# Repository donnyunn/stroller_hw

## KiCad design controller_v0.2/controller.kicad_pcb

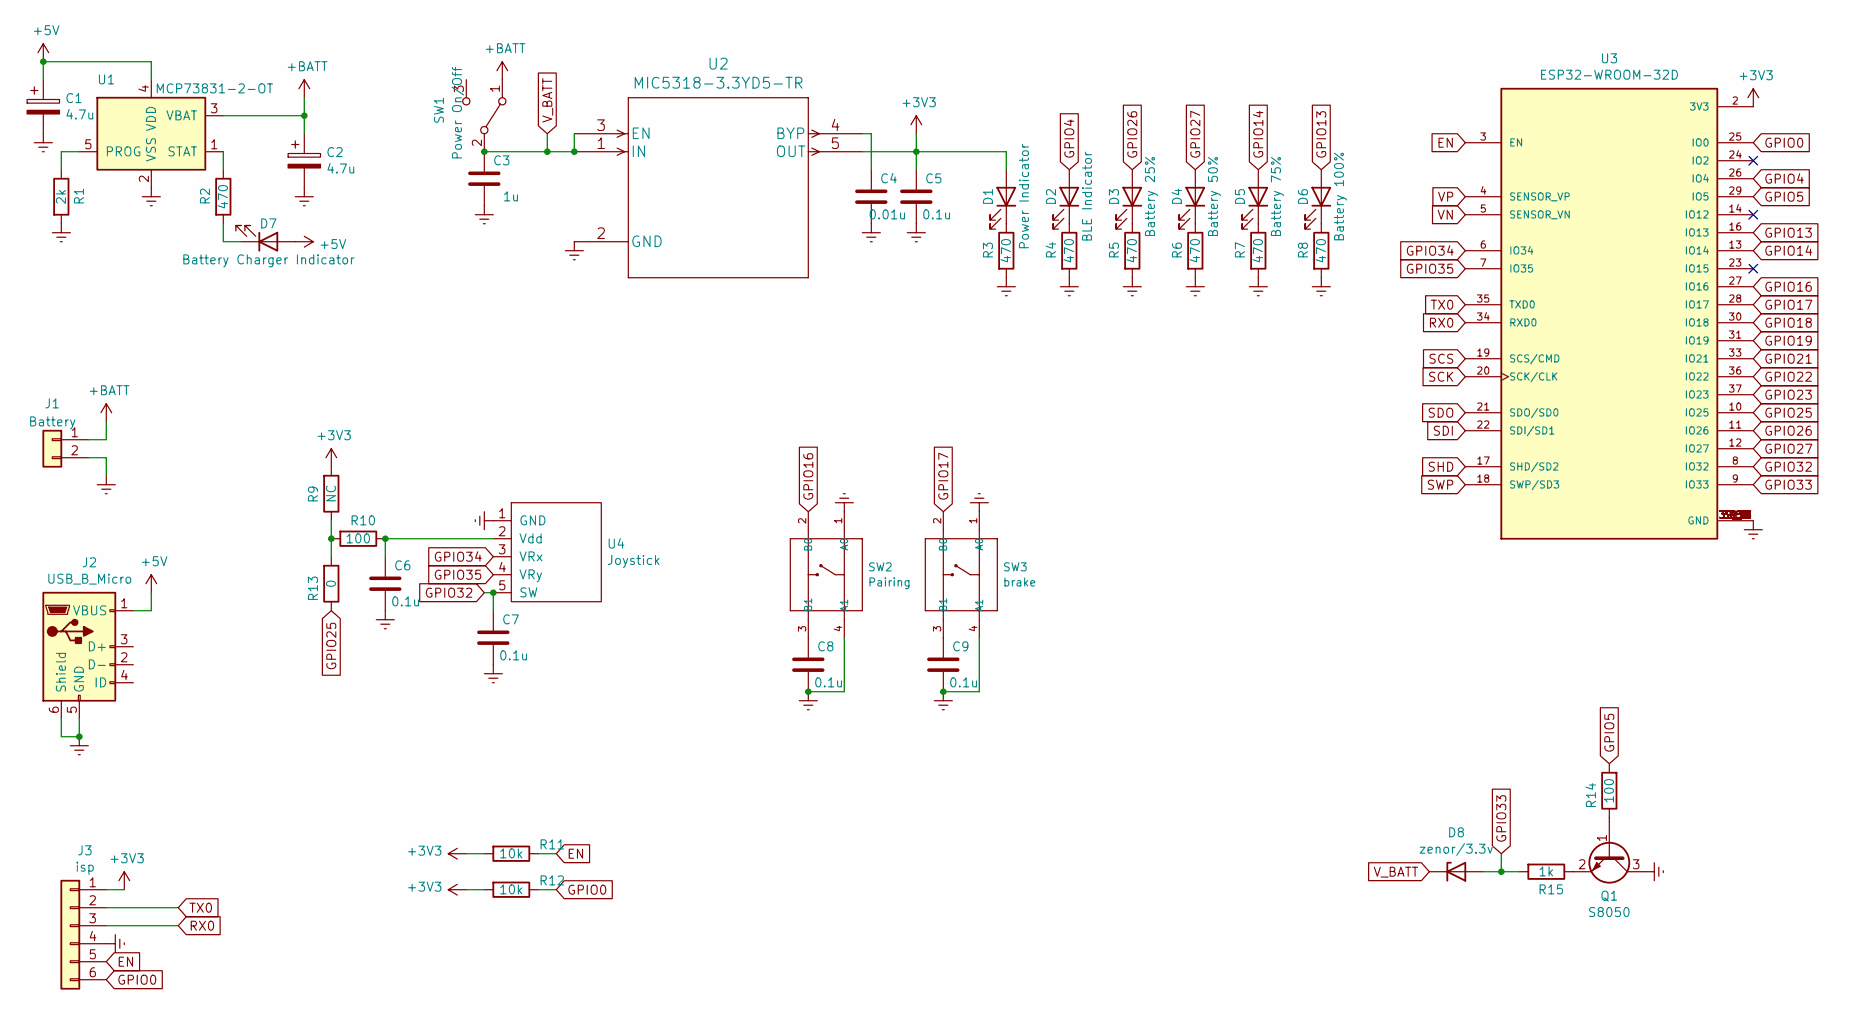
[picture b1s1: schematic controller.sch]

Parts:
C1, C2: 4.7u; CP_EIA-3216-18_Kemet-A; MPN TAJA475K006RNJ
C3: 1u; C_0603_1608Metric_Pad1.08x0.95mm_HandSolder; MPN CL10A105KQ8NNNC
C4: 0.01u; C_0603_1608Metric_Pad1.08x0.95mm_HandSolder; MPN CL10B103KB8NNNC
C5, C6, C7, C8, C9: 0.1u; C_0603_1608Metric_Pad1.08x0.95mm_HandSolder; MPN CL10B104KB8NNNL
D1: Power Indicator; LED_0805_2012Metric_Pad1.15x1.40mm_HandSolder; MPN WR148UW-W
D2: BLE Indicator; LED_0805_2012Metric_Pad1.15x1.40mm_HandSolder; MPN WR148UW-W
D3: Battery 25%; LED_0805_2012Metric_Pad1.15x1.40mm_HandSolder; MPN WR148UW-W
D4: Battery 50%; LED_0805_2012Metric_Pad1.15x1.40mm_HandSolder; MPN WR148UW-W
D5: Battery 75%; LED_0805_2012Metric_Pad1.15x1.40mm_HandSolder; MPN WR148UW-W
D6: Battery 100%; LED_0805_2012Metric_Pad1.15x1.40mm_HandSolder; MPN WR148UW-W
D7: Battery Charger Indicator; LED_0805_2012Metric_Pad1.15x1.40mm_HandSolder; MPN WR148UW-W
D8: zenor/3.3v; D_T-1_P5.08mm_Horizontal
J1: Battery; Molex_PicoBlade_53261-0271_1x02-1MP_P1.25mm_Horizontal; MPN 0532610271
J2: USB_B_Micro; USB_Micro-B_GCT_USB3076-30-A; MPN USB3076-30-A
J3: isp; JST_PH_B6B-PH-K_1x06_P2.00mm_Vertical; MPN B6B-PH-K-S(LF)(SN)
Q1: S8050; SOT-23
R1: 2k; R_0603_1608Metric_Pad0.98x0.95mm_HandSolder; MPN RC0603FR-072KL
R2, R3, R4, R5, R6, R7, R8: 470; R_0603_1608Metric_Pad0.98x0.95mm_HandSolder; MPN RC0603JR-07470RL
R9: NC; R_0603_1608Metric_Pad0.98x0.95mm_HandSolder
R10: 100; R_0603_1608Metric_Pad0.98x0.95mm_HandSolder; MPN RC0603JR-07100RL
R11, R12: 10k; R_0603_1608Metric_Pad0.98x0.95mm_HandSolder; MPN AC0603JR-0710KL
R13: 0; R_0603_1608Metric_Pad0.98x0.95mm_HandSolder; MPN RC0603FR-070RL
R14: 100; R_0603_1608Metric_Pad0.98x0.95mm_HandSolder
R15: 1k; R_0603_1608Metric_Pad0.98x0.95mm_HandSolder
SW1: Power On/Off; PinHeader_1x03_P2.54mm_Vertical
SW2: Pairing; SW4-6.0X6.0X5.0MM; MPN TS-1105-8MM
SW3: brake; SW4-6.0X6.0X5.0MM; MPN TS-1105
U1: MCP73831-2-OT; SOT-23-5; MPN MCP73831T-2ACI/OT
U2: MIC5318-3.3YD5-TR; MPN MIC5318-3.3YD5-TR
U3: ESP32-WROOM-32D; MODULE_ESP32-WROOM-32D; MPN ESP32-WROOM-32D
U4: Joystick; EPX389MK; MPN 조이스틱 스위치-TS

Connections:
+3V3: C5.1, D1.2 (A), J3.1, R9.2, R11.2, R12.2, U2.5 (OUT), U3.2 (3V3)
+5V: C1.1, D7.2 (A), J2.1 (VBUS), U1.4 (VDD)
+BATT: C2.1, J1.1, SW1.1 (A), U1.3 (VBAT)
EN: J3.5, R11.1, U3.3 (EN)
Earth: C1.2, C2.2, C3.2, C4.2, C5.2, C6.2, C7.2, C8.2, C9.2, J1.2, J2.5 (GND), J2.6 (Shield), J3.4, Q1.3 (C), R1.2, R3.2, R4.2, R5.2, R6.2, R7.2, R8.2, SW2.1 (A0), SW2.4 (A1), SW3.1 (A0), SW3.4 (A1), U1.2 (VSS), U2.2 (GND), U3.1 (GND), U3.15 (GND), U3.38 (GND), U3.39_1 (GND), U3.39_2 (GND), U3.39_3 (GND), U3.39_4 (GND), U3.39_5 (GND), U3.39_6 (GND), U3.39_7 (GND), U3.39_8 (GND), U3.39_9 (GND), U3.39_10 (GND), U3.39_11 (GND), U3.39_12 (GND), U3.39_13 (GND), U3.39_14 (GND), U3.39_15 (GND), U3.39_16 (GND), U3.39_17 (GND), U3.39_18 (GND), U3.39_19 (GND), U3.39_20 (GND), U3.39_21 (GND), U4.1 (GND)
GPIO0: J3.6, R12.1, U3.25 (IO0)
GPIO4: D2.2 (A), U3.26 (IO4)
GPIO5: R14.2, U3.29 (IO5)
GPIO13: D6.2 (A), U3.16 (IO13)
GPIO14: D5.2 (A), U3.13 (IO14)
GPIO16: SW2.2 (B0), U3.27 (IO16)
GPIO17: SW3.2 (B0), U3.28 (IO17)
GPIO18: U3.30 (IO18)
GPIO19: U3.31 (IO19)
GPIO21: U3.33 (IO21)
GPIO22: U3.36 (IO22)
GPIO23: U3.37 (IO23)
GPIO25: R13.1, U3.10 (IO25)
GPIO26: D3.2 (A), U3.11 (IO26)
GPIO27: D4.2 (A), U3.12 (IO27)
GPIO32: C7.1, U3.8 (IO32), U4.5 (SW)
GPIO33: D8.2 (A), R15.2, U3.9 (IO33)
GPIO34: U3.6 (IO34), U4.3 (VRx)
GPIO35: U3.7 (IO35), U4.4 (VRy)
unnamed: C4.1, U2.4 (BYP)
unnamed: C6.1, R10.1, U4.2 (Vdd)
unnamed: C8.1, SW2.3 (B1)
unnamed: C9.1, SW3.3 (B1)
unnamed: D1.1 (K), R3.1
unnamed: D2.1 (K), R4.1
unnamed: D3.1 (K), R5.1
unnamed: D4.1 (K), R6.1
unnamed: D5.1 (K), R7.1
unnamed: D6.1 (K), R8.1
unnamed: D7.1 (K), R2.2
unnamed: Q1.1 (B), R14.1
unnamed: Q1.2 (E), R15.1
unnamed: R1.1, U1.5 (PROG)
unnamed: R2.1, U1.1 (STAT)
unnamed: R9.1, R10.2, R13.2
RX0: J3.3, U3.34 (RXD0)
SCK: U3.20 (SCK/CLK)
SCS: U3.19 (SCS/CMD)
SDI: U3.22 (SDI/SD1)
SDO: U3.21 (SDO/SD0)
SHD: U3.17 (SHD/SD2)
SWP: U3.18 (SWP/SD3)
TX0: J3.2, U3.35 (TXD0)
VN: U3.5 (SENSOR_VN)
VP: U3.4 (SENSOR_VP)
V_BATT: C3.1, D8.1 (K), SW1.2 (B), U2.1 (IN), U2.3 (EN)

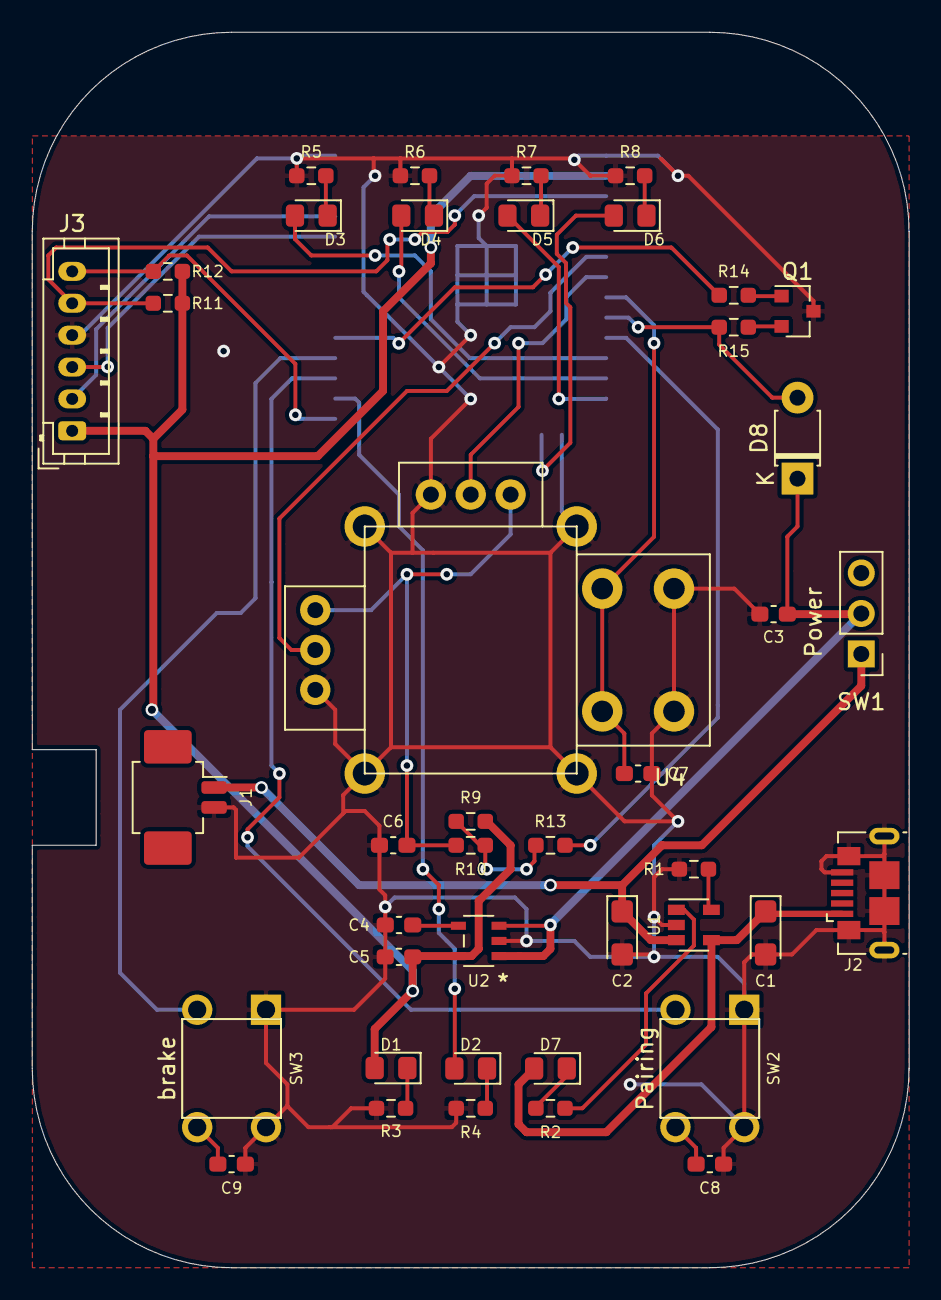
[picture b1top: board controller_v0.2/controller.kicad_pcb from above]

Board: 2 copper layers, 55.0 x 77.5 mm, 43 parts (1 on the bottom side), 38 nets.

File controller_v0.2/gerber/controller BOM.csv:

Reference, Quantity, Value, Footprint, Datasheet, MPN
C1 C2 ,2,"4.7u","Capacitor_Tantalum_SMD:CP_EIA-3216-18_Kemet-A","https://www.digikey.kr/product-detail/ko/avx-corporation/TAJ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","TAJA475K006RNJ"
C3 ,1,"1u","Capacitor_SMD:C_0603_1608Metric_Pad1.08x0.95mm_HandSolder","https://www.digikey.kr/product-detail/ko/samsung-electro-mec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","CL10A105KQ8NNNC"
C4 ,1,"0.01u","Capacitor_SMD:C_0603_1608Metric_Pad1.08x0.95mm_HandSolder","https://www.digikey.kr/product-detail/ko/samsung-electro-mec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","CL10B103KB8NNNC"
C5 C6 C7 C8 C9 C10 ,6,"0.1u","Capacitor_SMD:C_0603_1608Metric_Pad1.08x0.95mm_HandSolder","https://www.digikey.kr/product-detail/ko/samsung-electro-mec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","CL10B104KB8NNNL"
D1 ,1,"Power Indicator","LED_SMD:LED_0805_2012Metric_Pad1.15x1.40mm_HandSolder","https://www.eleparts.co.kr/goods/view?no=8104621","WR148UW-W"
D2 ,1,"BLE Indicator","LED_SMD:LED_0805_2012Metric_Pad1.15x1.40mm_HandSolder","https://www.eleparts.co.kr/goods/view?no=8104621","WR148UW-W"
D3 ,1,"Battery 25%","LED_SMD:LED_0805_2012Metric_Pad1.15x1.40mm_HandSolder","https://www.eleparts.co.kr/goods/view?no=8104621","WR148UW-W"
D4 ,1,"Battery 50%","LED_SMD:LED_0805_2012Metric_Pad1.15x1.40mm_HandSolder","https://www.eleparts.co.kr/goods/view?no=8104621","WR148UW-W"
D5 ,1,"Battery 75%","LED_SMD:LED_0805_2012Metric_Pad1.15x1.40mm_HandSolder","https://www.eleparts.co.kr/goods/view?no=8104621","WR148UW-W"
D6 ,1,"Battery 100%","LED_SMD:LED_0805_2012Metric_Pad1.15x1.40mm_HandSolder","https://www.eleparts.co.kr/goods/view?no=8104621","WR148UW-W"
D7 ,1,"Battery Charger Indicator","LED_SMD:LED_0805_2012Metric_Pad1.15x1.40mm_HandSolder","https://www.eleparts.co.kr/goods/view?no=8104621","WR148UW-W"
J1 ,1,"Battery","Connector_Molex:Molex_PicoBlade_53261-0271_1x02-1MP_P1.25mm_Horizontal","https://www.digikey.kr/product-detail/ko/molex/0532610271/WM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","0532610271"
J2 ,1,"USB_B_Micro","Connector_USB:USB_Micro-B_GCT_USB3076-30-A","https://www.digikey.kr/product-detail/ko/gct/USB3076-30-A/20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","USB3076-30-A"
J3 ,1,"isp","Connector_JST:JST_PH_B6B-PH-K_1x06_P2.00mm_Vertical","https://www.eleparts.co.kr/goods/view?no=7600842","B6B-PH-K-S(LF)(SN)"
R1 ,1,"2k","Resistor_SMD:R_0603_1608Metric_Pad0.98x0.95mm_HandSolder","https://www.digikey.kr/product-detail/ko/yageo/RC0603FR-072K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","RC0603FR-072KL"
R10 ,1,"100","Resistor_SMD:R_0603_1608Metric_Pad0.98x0.95mm_HandSolder","https://www.digikey.kr/product-detail/ko/yageo/RC0603JR-0710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","RC0603JR-07100RL"
R11 R12 R14 R15 ,4,"10k","Resistor_SMD:R_0603_1608Metric_Pad0.98x0.95mm_HandSolder","https://www.digikey.kr/product-detail/ko/yageo/AC0603JR-0710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","AC0603JR-0710KL"
R13 ,1,"0","Resistor_SMD:R_0603_1608Metric_Pad0.98x0.95mm_HandSolder","https://www.digikey.kr/product-detail/ko/yageo/RC0603FR-070R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","RC0603FR-070RL"
R16 R17 ,2,"1k","Resistor_SMD:R_0603_1608Metric_Pad0.98x0.95mm_HandSolder","https://www.digikey.kr/product-detail/ko/yageo/RC0603JR-071K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","RC0603JR-071KL"
R2 R3 R4 R5 R6 R7 R8 ,7,"470","Resistor_SMD:R_0603_1608Metric_Pad0.98x0.95mm_HandSolder","https://www.digikey.kr/product-detail/ko/yageo/RC0603JR-0747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","RC0603JR-07470RL"
R9 ,1,"NC","Resistor_SMD:R_0603_1608Metric_Pad0.98x0.95mm_HandSolder","~"
SW1 ,1,"Power On/Off","Connector_PinHeader_2.54mm:PinHeader_1x03_P2.54mm_Vertical","~"
SW2 ,1,"Pairing","OPL_Switch:SW4-6.0X6.0X5.0MM","https://www.eleparts.co.kr/goods/view?no=2630843","TS-1105-8MM"
SW3 ,1,"brake","OPL_Switch:SW4-6.0X6.0X5.0MM","","TS-1105"
U1 ,1,"MCP73831-2-OT","Package_TO_SOT_SMD:SOT-23-5","http://ww1.microchip.com/downloads/en/DeviceDoc/20001984g.pdf","MCP73831T-2ACI/OT"
U2 ,1,"MIC5318-3.3YD5-TR","MIC531833YD5TR:MIC5318-3.3YD5-TR","https://www.digikey.kr/product-detail/ko/microchip-technolog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","MIC5318-3.3YD5-TR"
U3 ,1,"ESP32-WROOM-32D","ESP32-WROOM-32D:MODULE_ESP32-WROOM-32D","https://www.digikey.kr/product-detail/ko/espressif-systems/E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","ESP32-WROOM-32D"
U4 ,1,"Joystick","EPK389MK:EPX389MK","https://www.eleparts.co.kr/goods/view?no=32769","조이스틱 스위치-TS"
U5 ,1,"MAX17048G+T10","MAX17048G_T10:MAX17048G_T10","https://www.digikey.kr/product-detail/ko/maxim-integrated/MA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","MAX17048G+T10"

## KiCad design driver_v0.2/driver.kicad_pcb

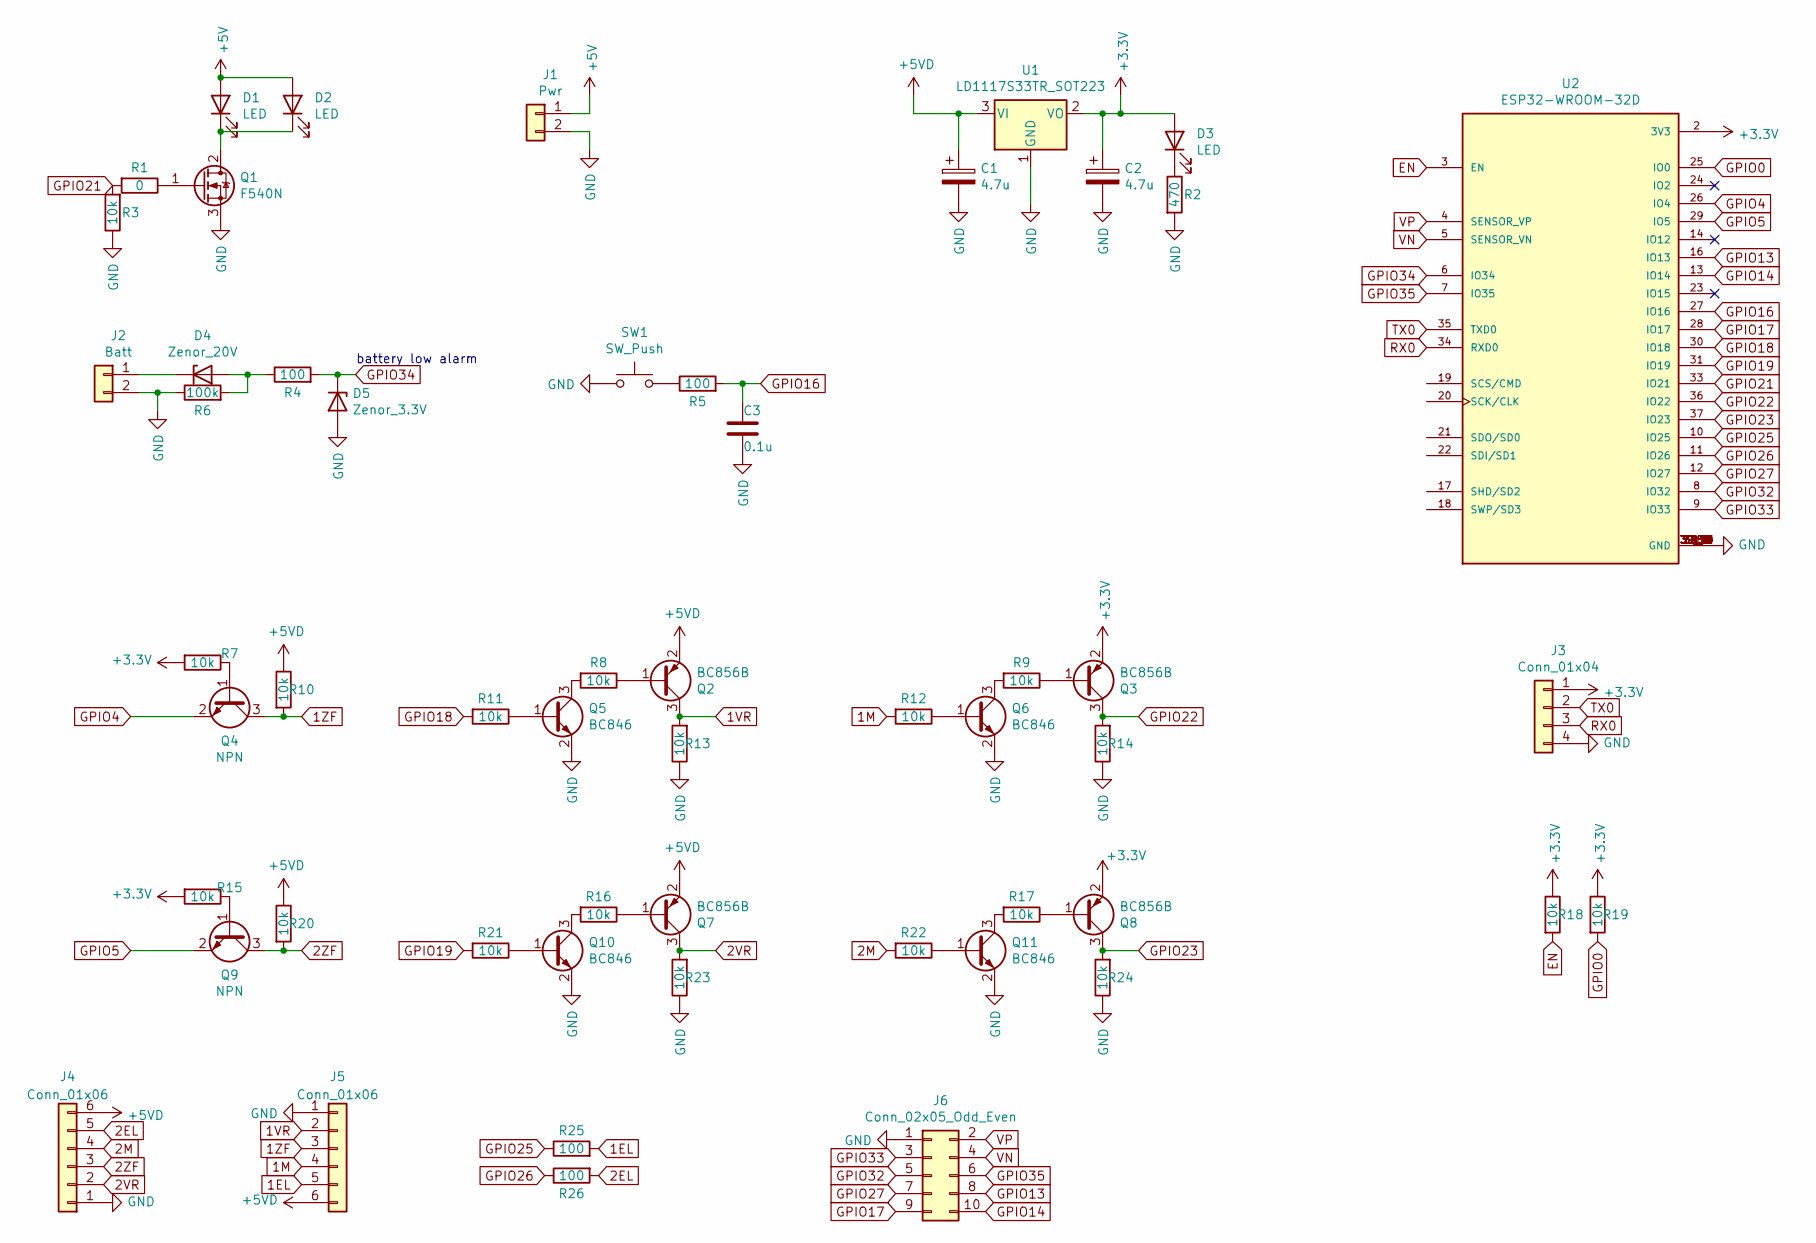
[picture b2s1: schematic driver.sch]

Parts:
C1, C2: 4.7u; CP_EIA-3216-18_Kemet-A
C3: 0.1u; C_0603_1608Metric_Pad1.08x0.95mm_HandSolder
D1, D2: LED; LED_D5.0mm
D3: LED; LED_0805_2012Metric_Pad1.15x1.40mm_HandSolder; MPN WR148UW-W
D4: Zenor_20V; D_DO-41_SOD81_P7.62mm_Horizontal; MPN 1N4747A
D5: Zenor_3.3V; D_DO-41_SOD81_P7.62mm_Horizontal; MPN 1N5226B
J1: Pwr; PinHeader_1x02_P2.54mm_Vertical
J2: Batt; PinHeader_1x02_P2.54mm_Vertical
J3: Conn_01x04; PinHeader_1x04_P2.54mm_Vertical
J4, J5: Conn_01x06; JST_PH_B6B-PH-K_1x06_P2.00mm_Vertical
J6: Conn_02x05_Odd_Even; PinHeader_2x05_P2.54mm_Vertical
Q1: F540N; TO-220-3_Vertical
Q2, Q3, Q7, Q8: BC856B; SOT-23
Q4, Q9: NPN; SOT-23; MPN S8050
Q5, Q6, Q10, Q11: BC846; SOT-23
R1: 0; R_0603_1608Metric_Pad0.98x0.95mm_HandSolder
R2: 470; R_0603_1608Metric_Pad0.98x0.95mm_HandSolder
R3, R7, R8, R9, R10, R11, R12, R13, R14, R15, R16, R17, R18, R19, R20, R21, R22, R23, R24: 10k; R_0603_1608Metric_Pad0.98x0.95mm_HandSolder
R4, R5, R25, R26: 100; R_0603_1608Metric_Pad0.98x0.95mm_HandSolder
R6: 100k; R_0603_1608Metric_Pad0.98x0.95mm_HandSolder
SW1: SW_Push; SW_PUSH_6mm; MPN TS-1105-8MM
U1: LD1117S33TR_SOT223; SOT-223-3_TabPin2; MPN ZLDO1117QG33TA
U2: ESP32-WROOM-32D; ESP32-WROOM-32; PARTREV 1.9

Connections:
1EL: J5.5, R25.2
1M: J5.4, R12.2
1VR: J5.2, Q2.3 (C), R13.2
1ZF: J5.3, Q4.3 (C), R10.2
2EL: J4.5, R26.2
2M: J4.4, R22.2
2VR: J4.2, Q7.3 (C), R23.2
2ZF: J4.3, Q9.3 (C), R20.2
+3V3: C2.1, D3.2 (A), J3.1, Q3.2 (E), Q8.2 (E), R7.2, R15.2, R18.1, R19.1, U1.2 (VO), U2.2 (3V3)
+5V: D1.2 (A), D2.2 (A), J1.1
+5VD: C1.1, J4.6, J5.6, Q2.2 (E), Q7.2 (E), R10.1, R20.1, U1.3 (VI)
EN: R18.2, U2.3 (EN)
GND: C1.2, C2.2, C3.2, D5.2 (A), J1.2, J2.2, J3.4, J4.1, J5.1, J6.1, Q1.3 (S), Q5.2 (E), Q6.2 (E), Q10.2 (E), Q11.2 (E), R2.2, R3.1, R6.1, R13.1, R14.1, R23.1, R24.1, SW1.1, U1.1 (GND), U2.1 (GND), U2.15 (GND), U2.38 (GND), U2.39_1 (GND), U2.39_2 (GND), U2.39_3 (GND), U2.39_4 (GND), U2.39_5 (GND), U2.39_6 (GND), U2.39_7 (GND), U2.39_8 (GND), U2.39_9 (GND), U2.39_10 (GND), U2.39_11 (GND), U2.39_12 (GND), U2.39_13 (GND), U2.39_14 (GND), U2.39_15 (GND), U2.39_16 (GND), U2.39_17 (GND), U2.39_18 (GND), U2.39_19 (GND), U2.39_20 (GND), U2.39_21 (GND)
GPIO0: R19.2, U2.25 (IO0)
GPIO4: Q4.2 (E), U2.26 (IO4)
GPIO5: Q9.2 (E), U2.29 (IO5)
GPIO13: J6.8, U2.16 (IO13)
GPIO14: J6.10, U2.13 (IO14)
GPIO16: C3.1, R5.2, U2.27 (IO16)
GPIO17: J6.9, U2.28 (IO17)
GPIO18: R11.2, U2.30 (IO18)
GPIO19: R21.2, U2.31 (IO19)
GPIO21: R1.2, R3.2, U2.33 (IO21)
GPIO22: Q3.3 (C), R14.2, U2.36 (IO22)
GPIO23: Q8.3 (C), R24.2, U2.37 (IO23)
GPIO25: R25.1, U2.10 (IO25)
GPIO26: R26.1, U2.11 (IO26)
GPIO27: J6.7, U2.12 (IO27)
GPIO32: J6.5, U2.8 (IO32)
GPIO33: J6.3, U2.9 (IO33)
GPIO34: D5.1 (K), R4.2, U2.6 (IO34)
GPIO35: J6.6, U2.7 (IO35)
unnamed: D1.1 (K), D2.1 (K), Q1.2 (D)
unnamed: D3.1 (K), R2.1
unnamed: D4.1 (K), J2.1
unnamed: D4.2 (A), R4.1, R6.2
unnamed: Q1.1 (G), R1.1
unnamed: Q2.1 (B), R8.1
unnamed: Q3.1 (B), R9.1
unnamed: Q4.1 (B), R7.1
unnamed: Q5.1 (B), R11.1
unnamed: Q5.3 (C), R8.2
unnamed: Q6.1 (B), R12.1
unnamed: Q6.3 (C), R9.2
unnamed: Q7.1 (B), R16.1
unnamed: Q8.1 (B), R17.1
unnamed: Q9.1 (B), R15.1
unnamed: Q10.1 (B), R21.1
unnamed: Q10.3 (C), R16.2
unnamed: Q11.1 (B), R22.1
unnamed: Q11.3 (C), R17.2
unnamed: R5.1, SW1.2
RX0: J3.3, U2.34 (RXD0)
TX0: J3.2, U2.35 (TXD0)
VN: J6.4, U2.5 (SENSOR_VN)
VP: J6.2, U2.4 (SENSOR_VP)

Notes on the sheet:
battery low alarm

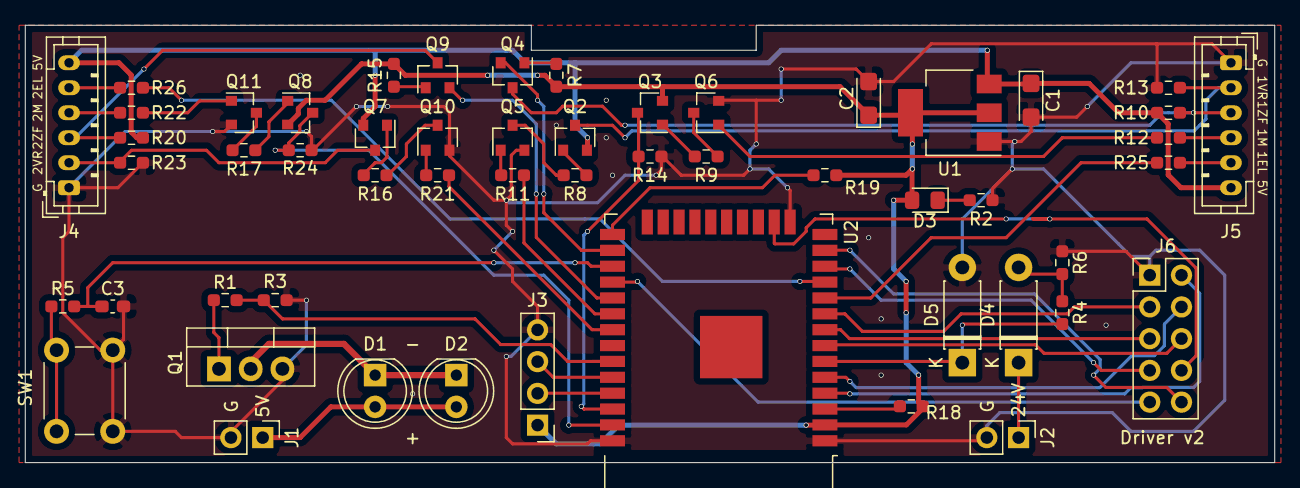
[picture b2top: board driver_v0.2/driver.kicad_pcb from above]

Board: 2 copper layers, 100.0 x 35.0 mm, 54 parts (0 on the bottom side), 56 nets.

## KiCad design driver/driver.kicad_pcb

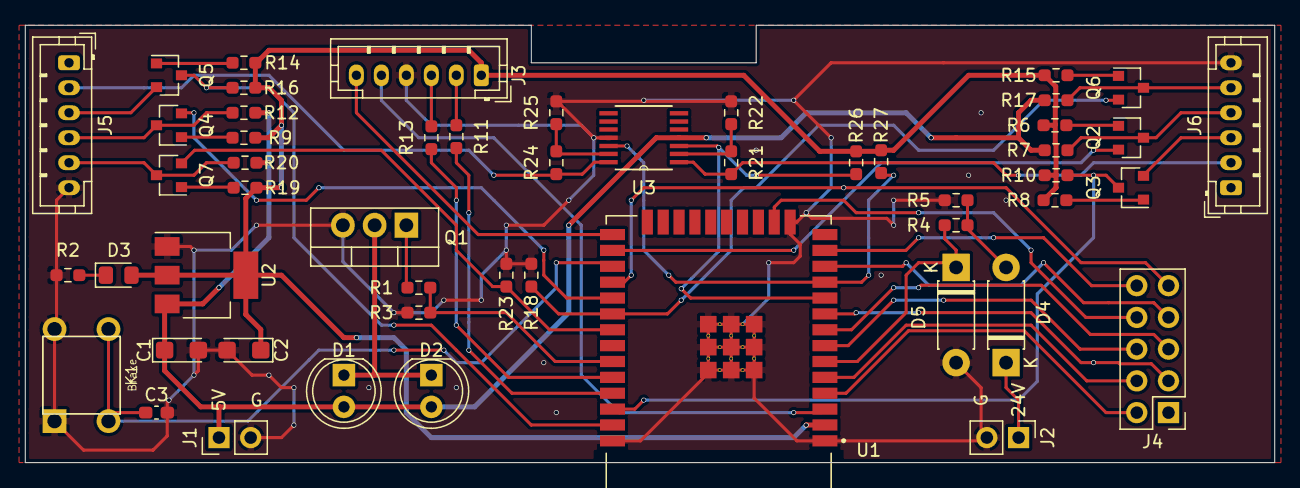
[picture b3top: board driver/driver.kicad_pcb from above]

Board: 2 copper layers, 100.0 x 35.0 mm, 52 parts (0 on the bottom side), 50 nets.

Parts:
C1, C2: 4.7u; CP_EIA-3216-18_Kemet-A
C3: 0.1u; C_0603_1608Metric_Pad1.08x0.95mm_HandSolder
D1, D2: LED; LED_D5.0mm
D3: LED; LED_0805_2012Metric_Pad1.15x1.40mm_HandSolder
D4: Zenor_20V; D_DO-41_SOD81_P7.62mm_Horizontal
D5: Zenor_3.3V; D_DO-41_SOD81_P7.62mm_Horizontal
J1: Pwr; PinHeader_1x02_P2.54mm_Vertical
J2: Batt; PinHeader_1x02_P2.54mm_Vertical
J3: isp; JST_PH_B6B-PH-K_1x06_P2.00mm_Vertical
J4: Conn_02x05_Odd_Even; PinHeader_2x05_P2.54mm_Vertical
J5, J6: Conn_01x06; JST_PH_B6B-PH-K_1x06_P2.00mm_Vertical
K1: Brake; SW4-6.0X6.0X5.0MM
Q1: IRF540N; TO-220-3_Vertical
Q2, Q3, Q4, Q5, Q6, Q7: NPN; SOT-23
R1, R11, R13, R18, R22, R23, R25: 1k; R_0603_1608Metric_Pad0.98x0.95mm_HandSolder
R2: 470; R_0603_1608Metric_Pad0.98x0.95mm_HandSolder
R3, R6, R7, R8, R9, R10, R12, R14, R15, R16, R17, R19, R20, R26, R27: 10k; R_0603_1608Metric_Pad0.98x0.95mm_HandSolder
R4: 100; R_0603_1608Metric_Pad0.98x0.95mm_HandSolder
R5: 100k; R_0603_1608Metric_Pad0.98x0.95mm_HandSolder
R21, R24: 560; R_0603_1608Metric_Pad0.98x0.95mm_HandSolder
U1: ESP32-WROOM-32D; MODULE_ESP32-WROOM-32D
U2: LD1117S33TR_SOT223; SOT-223-3_TabPin2
U3: MCP6044T-I_ST; MCP6044T

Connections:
1EL: J6.2, R21.2, U3.1
1M: J6.3, Q3.2
1VR: J6.5, Q6.3, R17.2
1ZF: J6.4, Q2.3, R7.2
2EL: J5.2, R24.2, U3.14
2M: J5.3, Q5.2
2VR: J5.5, Q7.3, R20.2
2ZF: J5.4, Q4.3, R12.2
+3V3: C2.1, D3.2, J3.1, R6.2, R8.2, R9.2, R10.1, R14.2, R15.2, R16.1, R19.2, R26.2, R27.2, U1.2, U2.2
+5V: C1.1, D1.2, D2.2, J1.1, R7.1, R12.1, R17.1, R20.1, U2.3, U3.4
EN: J3.5, U1.3
GND: C1.2, C2.2, C3.2, D5.2, J1.2, J2.2, J3.4, J5.6, J6.6, K1.1, K1.4, Q1.3, R2.2, R3.1, R5.1, R18.2, R22.2, R23.2, R25.2, U1.1, U1.15, U1.38, U1.39_1, U1.39_2, U1.39_3, U1.39_4, U1.39_5, U1.39_6, U1.39_7, U1.39_8, U1.39_9, U1.39_10, U1.39_11, U1.39_12, U1.39_13, U1.39_14, U1.39_15, U1.39_16, U1.39_17, U1.39_18, U1.39_19, U1.39_20, U1.39_21, U2.1, U3.11
GPIO0: J3.6, U1.25
GPIO4: Q2.2, U1.26
GPIO5: Q4.2, U1.29
GPIO13: J4.8, U1.16
GPIO14: J4.10, U1.13
GPIO16: C3.1, K1.2, K1.3, U1.27
GPIO17: J4.9, U1.28
GPIO18: Q6.2, R18.1, U1.30
GPIO19: Q7.2, R23.1, U1.31
GPIO21: R1.2, R3.2, U1.33
GPIO22: Q3.3, R10.2, U1.36
GPIO23: Q5.3, R16.2, U1.37
GPIO25: R26.1, U1.10, U3.3
GPIO26: R27.1, U1.11, U3.12
GPIO27: J4.7, U1.12
GPIO32: J4.5, U1.8
GPIO33: J4.3, U1.9
GPIO34: D5.1, R4.2, U1.6
GPIO35: J4.6, U1.7
unnamed: D1.1, D2.1, Q1.2
unnamed: D3.1, R2.1
unnamed: D4.1, J2.1
unnamed: D4.2, R4.1, R5.2
unnamed: J3.2, R11.2
unnamed: J3.3, R13.2
unnamed: Q1.1, R1.1
unnamed: Q2.1, R6.1
unnamed: Q3.1, R8.1
unnamed: Q4.1, R9.1
unnamed: Q5.1, R14.1
unnamed: Q6.1, R15.1
unnamed: Q7.1, R19.1
unnamed: R21.1, R22.1, U3.2
unnamed: R24.1, R25.1, U3.13
RX0: R13.1, U1.34
TX0: R11.1, U1.35
VN: J4.4, U1.5
VP: J4.2, U1.4

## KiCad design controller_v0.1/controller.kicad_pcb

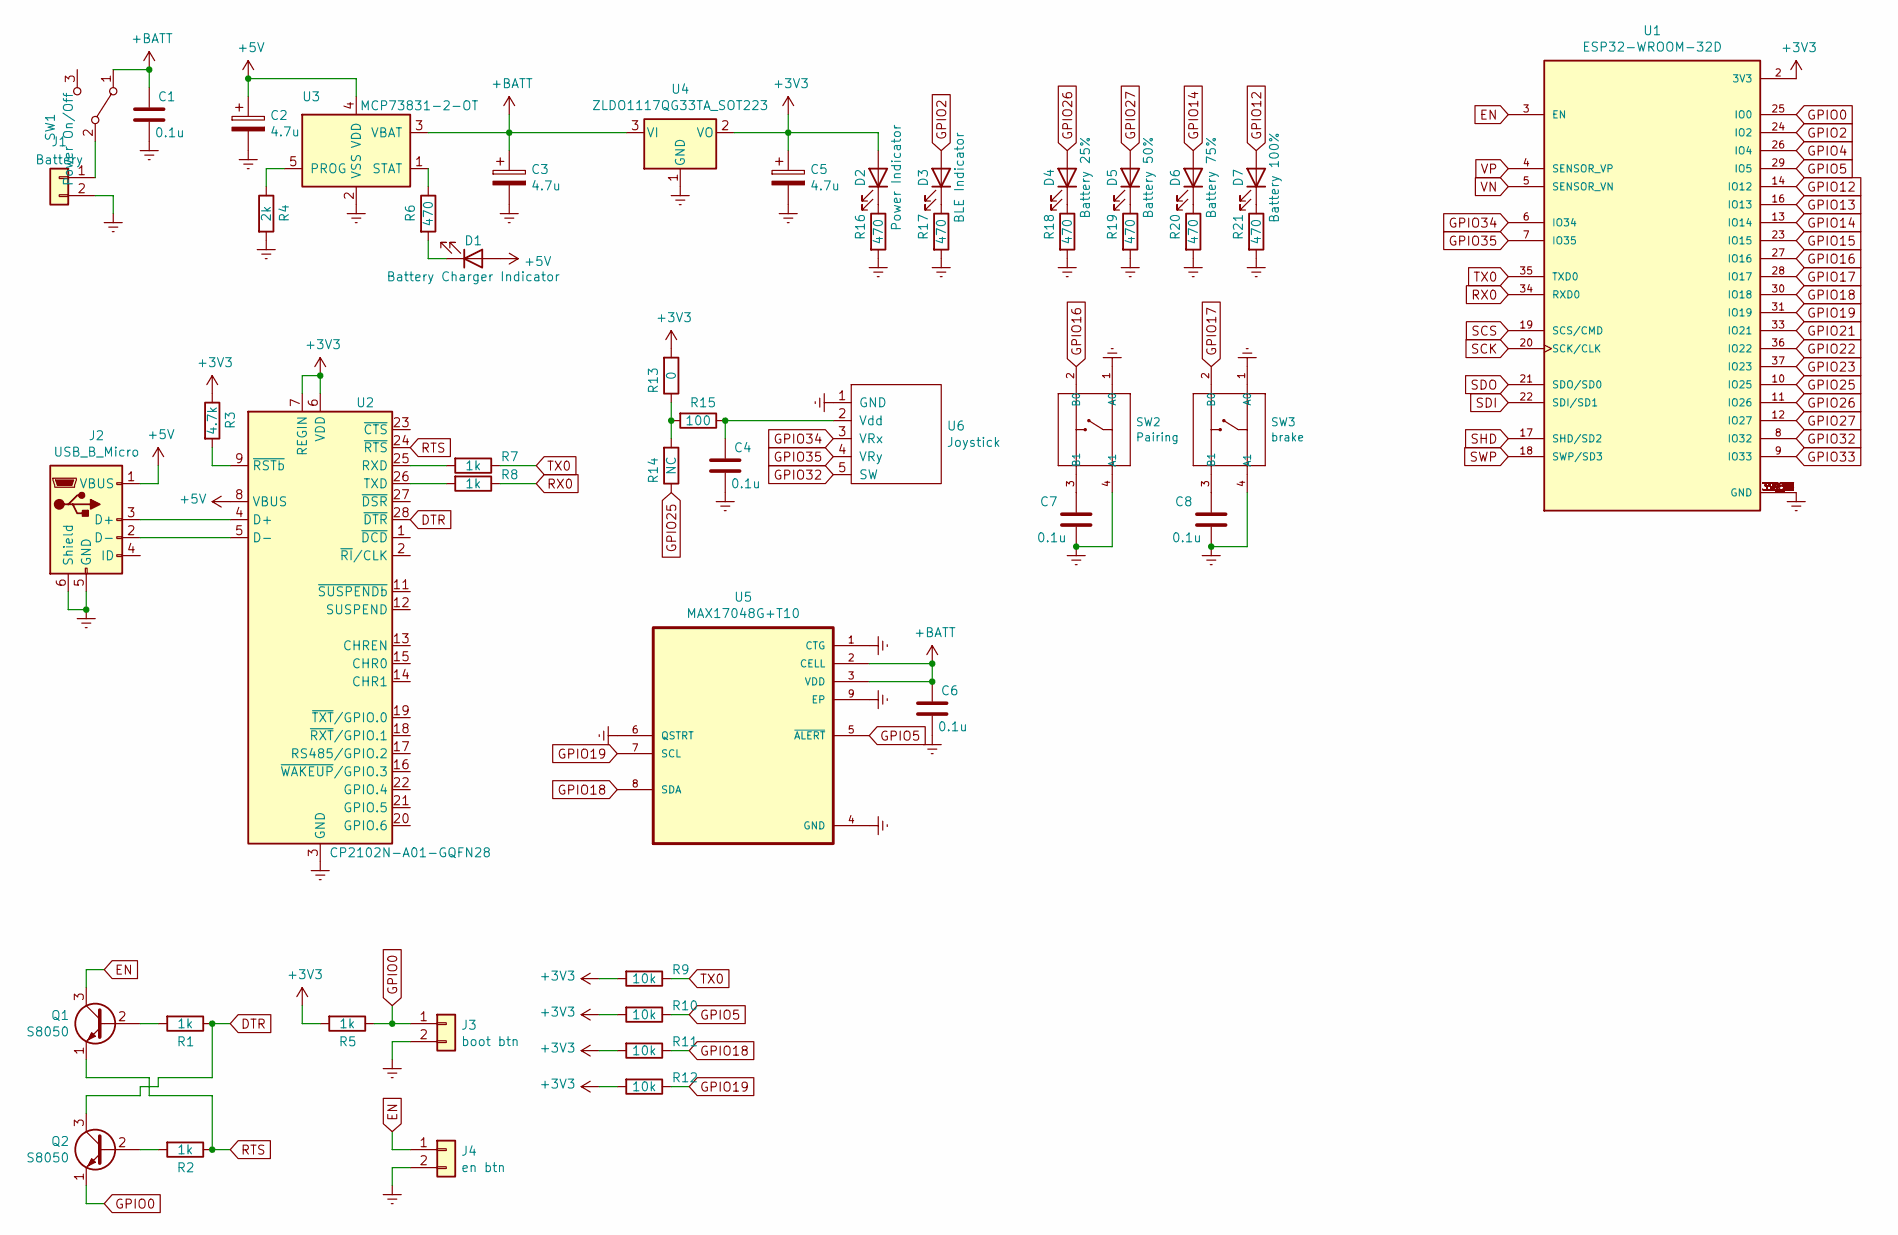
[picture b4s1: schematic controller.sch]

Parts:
C1, C4, C6, C7, C8: 0.1u; C_0603_1608Metric_Pad1.08x0.95mm_HandSolder
C2, C3, C5: 4.7u; CP_EIA-3216-18_Kemet-A
D1: Battery Charger Indicator; LED_D5.0mm
D2: Power Indicator; LED_D5.0mm
D3: BLE Indicator; LED_D5.0mm
D4: Battery 25%; LED_D5.0mm
D5: Battery 50%; LED_D5.0mm
D6: Battery 75%; LED_D5.0mm
D7: Battery 100%; LED_D5.0mm
J1: Battery; Molex_PicoBlade_53261-0271_1x02-1MP_P1.25mm_Horizontal
J2: USB_B_Micro; USB_Micro-B_Molex-105017-0001; MPN 47589-0001
J3: boot btn; PinHeader_1x02_P2.54mm_Vertical
J4: en btn; PinHeader_1x02_P2.54mm_Vertical
Q1, Q2: S8050; SOT-23; MPN S8050
R1, R2, R5, R7, R8: 1k; R_0603_1608Metric_Pad0.98x0.95mm_HandSolder
R3: 4.7k; R_0603_1608Metric_Pad0.98x0.95mm_HandSolder
R4: 2k; R_0603_1608Metric_Pad0.98x0.95mm_HandSolder
R6, R16, R17, R18, R19, R20, R21: 470; R_0603_1608Metric_Pad0.98x0.95mm_HandSolder
R9, R10, R11, R12: 10k; R_0603_1608Metric_Pad0.98x0.95mm_HandSolder
R13: 0; R_0603_1608Metric_Pad0.98x0.95mm_HandSolder
R14: NC; R_0603_1608Metric_Pad0.98x0.95mm_HandSolder
R15: 100; R_0603_1608Metric_Pad0.98x0.95mm_HandSolder
SW1: Power On/Off; PinHeader_1x03_P2.54mm_Vertical
SW2: Pairing; SW4-6.0X6.0X5.0MM; MPN TS-1105
SW3: brake; SW4-6.0X6.0X5.0MM; MPN TS-1105
U1: ESP32-WROOM-32D; MODULE_ESP32-WROOM-32D; PARTREV 1.9
U2: CP2102N-A01-GQFN28; QFN-28-1EP_5x5mm_P0.5mm_EP3.35x3.35mm
U3: MCP73831-2-OT; SOT-23-5; MPN MCP73831T-2ACI/OT
U4: ZLDO1117QG33TA_SOT223; SOT-223-3_TabPin2; MPN ZLDO1117QG33TA
U5: MAX17048G+T10; MAX17048G_T10; MPN MAX17048G+T10
U6: Joystick; EPX389MK

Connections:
+3V3: C5.1, D2.2 (A), R3.1, R5.2, R9.2, R10.2, R11.2, R12.2, R13.2, U1.2 (3V3), U2.6 (VDD), U2.7 (REGIN), U4.2 (VO)
+5V: C2.1, D1.2 (A), J2.1 (VBUS), U2.8 (VBUS), U3.4 (VDD)
+BATT: C1.1, C3.1, C6.1, SW1.1 (A), U3.3 (VBAT), U4.3 (VI), U5.2 (CELL), U5.3 (VDD)
DTR: Q2.3 (C), R1.1, U2.28 (~DTR)
EN: J4.1, Q1.3 (C), U1.3 (EN)
Earth: C1.2, C2.2, C3.2, C4.2, C5.2, C6.2, C7.2, C8.2, J1.2, J2.5 (GND), J2.6 (Shield), J3.2, J4.2, R4.2, R16.2, R17.2, R18.2, R19.2, R20.2, R21.2, SW2.1 (A0), SW2.4 (A1), SW3.1 (A0), SW3.4 (A1), U1.1 (GND), U1.15 (GND), U1.38 (GND), U1.39_1 (GND), U1.39_2 (GND), U1.39_3 (GND), U1.39_4 (GND), U1.39_5 (GND), U1.39_6 (GND), U1.39_7 (GND), U1.39_8 (GND), U1.39_9 (GND), U1.39_10 (GND), U1.39_11 (GND), U1.39_12 (GND), U1.39_13 (GND), U1.39_14 (GND), U1.39_15 (GND), U1.39_16 (GND), U1.39_17 (GND), U1.39_18 (GND), U1.39_19 (GND), U1.39_20 (GND), U1.39_21 (GND), U2.3 (GND), U2.29 (GND), U3.2 (VSS), U4.1 (GND), U5.1 (CTG), U5.4 (GND), U5.6 (QSTRT), U5.9 (EP), U6.1 (GND)
GPIO0: J3.1, Q2.1 (E), R5.1, U1.25 (IO0)
GPIO2: D3.2 (A), U1.24 (IO2)
GPIO4: U1.26 (IO4)
GPIO5: R10.1, U1.29 (IO5), U5.5 (~ALERT)
GPIO12: D7.2 (A), U1.14 (IO12)
GPIO13: U1.16 (IO13)
GPIO14: D6.2 (A), U1.13 (IO14)
GPIO15: U1.23 (IO15)
GPIO16: SW2.2 (B0), U1.27 (IO16)
GPIO17: SW3.2 (B0), U1.28 (IO17)
GPIO18: R11.1, U1.30 (IO18), U5.8 (SDA)
GPIO19: R12.1, U1.31 (IO19), U5.7 (SCL)
GPIO21: U1.33 (IO21)
GPIO22: U1.36 (IO22)
GPIO23: U1.37 (IO23)
GPIO25: R14.1, U1.10 (IO25)
GPIO26: D4.2 (A), U1.11 (IO26)
GPIO27: D5.2 (A), U1.12 (IO27)
GPIO32: U1.8 (IO32), U6.5 (SW)
GPIO33: U1.9 (IO33)
GPIO34: U1.6 (IO34), U6.3 (VRx)
GPIO35: U1.7 (IO35), U6.4 (VRy)
unnamed: C4.1, R15.1, U6.2 (Vdd)
unnamed: C7.1, SW2.3 (B1)
unnamed: C8.1, SW3.3 (B1)
unnamed: D1.1 (K), R6.2
unnamed: D2.1 (K), R16.1
unnamed: D3.1 (K), R17.1
unnamed: D4.1 (K), R18.1
unnamed: D5.1 (K), R19.1
unnamed: D6.1 (K), R20.1
unnamed: D7.1 (K), R21.1
unnamed: J1.1, SW1.2 (B)
unnamed: J2.2 (D-), U2.5 (D-)
unnamed: J2.3 (D+), U2.4 (D+)
unnamed: Q1.2 (B), R1.2
unnamed: Q2.2 (B), R2.2
unnamed: R3.2, U2.9 (~RSTb)
unnamed: R4.1, U3.5 (PROG)
unnamed: R6.1, U3.1 (STAT)
unnamed: R7.2, U2.25 (RXD)
unnamed: R8.2, U2.26 (TXD)
unnamed: R13.1, R14.2, R15.2
RTS: Q1.1 (E), R2.1, U2.24 (~RTS)
RX0: R8.1, U1.34 (RXD0)
SCK: U1.20 (SCK/CLK)
SCS: U1.19 (SCS/CMD)
SDI: U1.22 (SDI/SD1)
SDO: U1.21 (SDO/SD0)
SHD: U1.17 (SHD/SD2)
SWP: U1.18 (SWP/SD3)
TX0: R7.1, R9.1, U1.35 (TXD0)
VN: U1.5 (SENSOR_VN)
VP: U1.4 (SENSOR_VP)

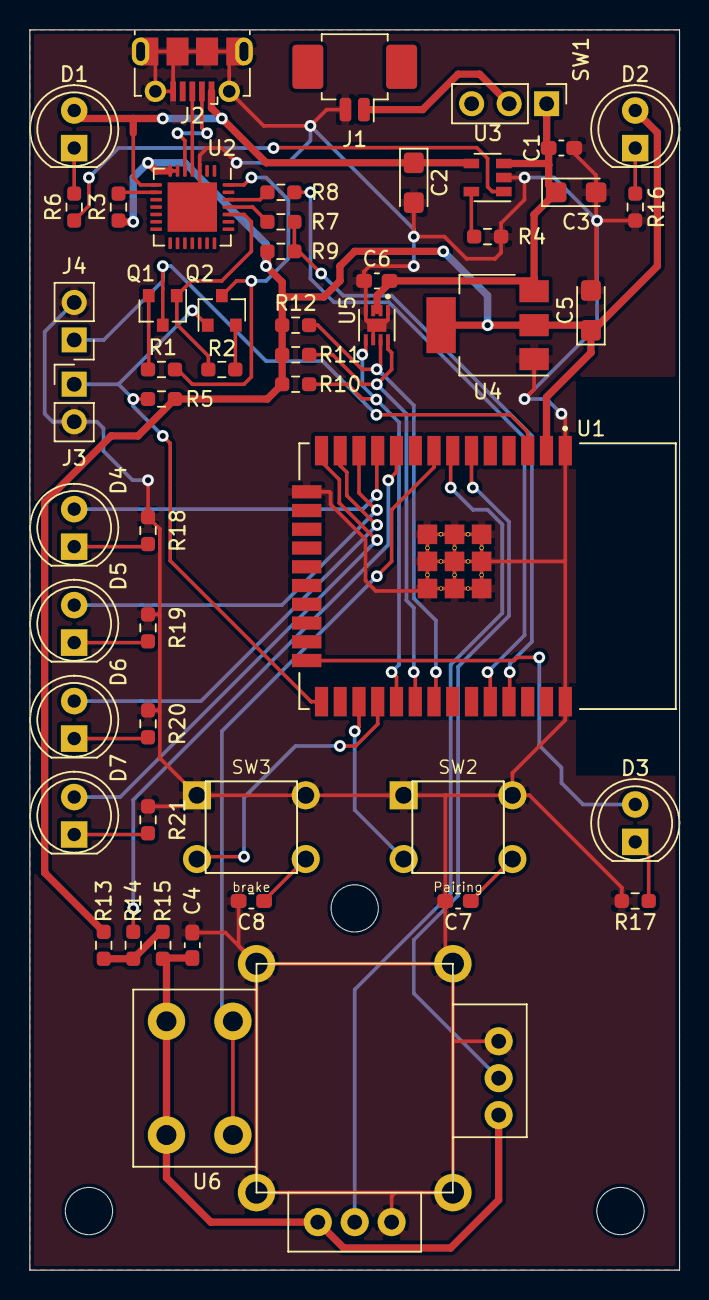
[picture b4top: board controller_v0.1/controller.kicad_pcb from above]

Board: 2 copper layers, 44.0 x 84.0 mm, 51 parts (0 on the bottom side), 45 nets.

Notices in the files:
parts and their libraries:
Copyright 2021 Accelerated Designs. All rights reserved.
